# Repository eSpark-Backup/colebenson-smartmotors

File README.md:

# ColeBenson-SmartMotors
 To create a smart motor system involving CAN Interface using STM32 MCU

## Project Requirements v3.3
* The RJ11 connector for CAN should be changed with RJ45 connector. The recommended connectors and pinouts are shared by client as stated below. We need to ensure that user can plug into any of the CAN connectors (CANA or CANB) and still have daisy chain feature without hassle. We will be restricting the user to only use Straight Through cable. 
    * ### Pinout Information

    * ### Recommended Connector
        * [Digikey Link](https://www.digikey.ca/en/products/detail/molex/0855115001/2421532); [Molex Link](https://www.molex.com/en-us/products/part-detail/855115001)

    * ### Question
      We need to check if we need to restrict the user to only connect from CANA to CANA or CANB to CANB or they can also connect from CANA to CANB in daisy chain?

* Remove all Solder bridges from the design from both Top Board and Bottom board. Following bridges were sent by Japan team but they need to be ensured.
    * [Top Board]  
      SB6  
      SB3  
      SB9  
      SB4  
      SB11  
      SB7  
      SB1  
    * [Bottom Board]  
      SB2  
      SB4  
      SB6  
      SB8

* Add another high current Stepper Motor connector to the design and add it overlapping the existing connector. The suggested connector is [Digikey Link](https://www.digikey.ca/en/products/detail/jst-sales-america-inc/B4P-VH-FB-B-LF-SN/7230471)
* Change boot mode to be able to use a single 1 x 3 header with the center pin always GND.
* Change XT60 connector this connector from [Robotshop](https://ca.robotshop.com/products/xt60-connector-male-female-pair-black)

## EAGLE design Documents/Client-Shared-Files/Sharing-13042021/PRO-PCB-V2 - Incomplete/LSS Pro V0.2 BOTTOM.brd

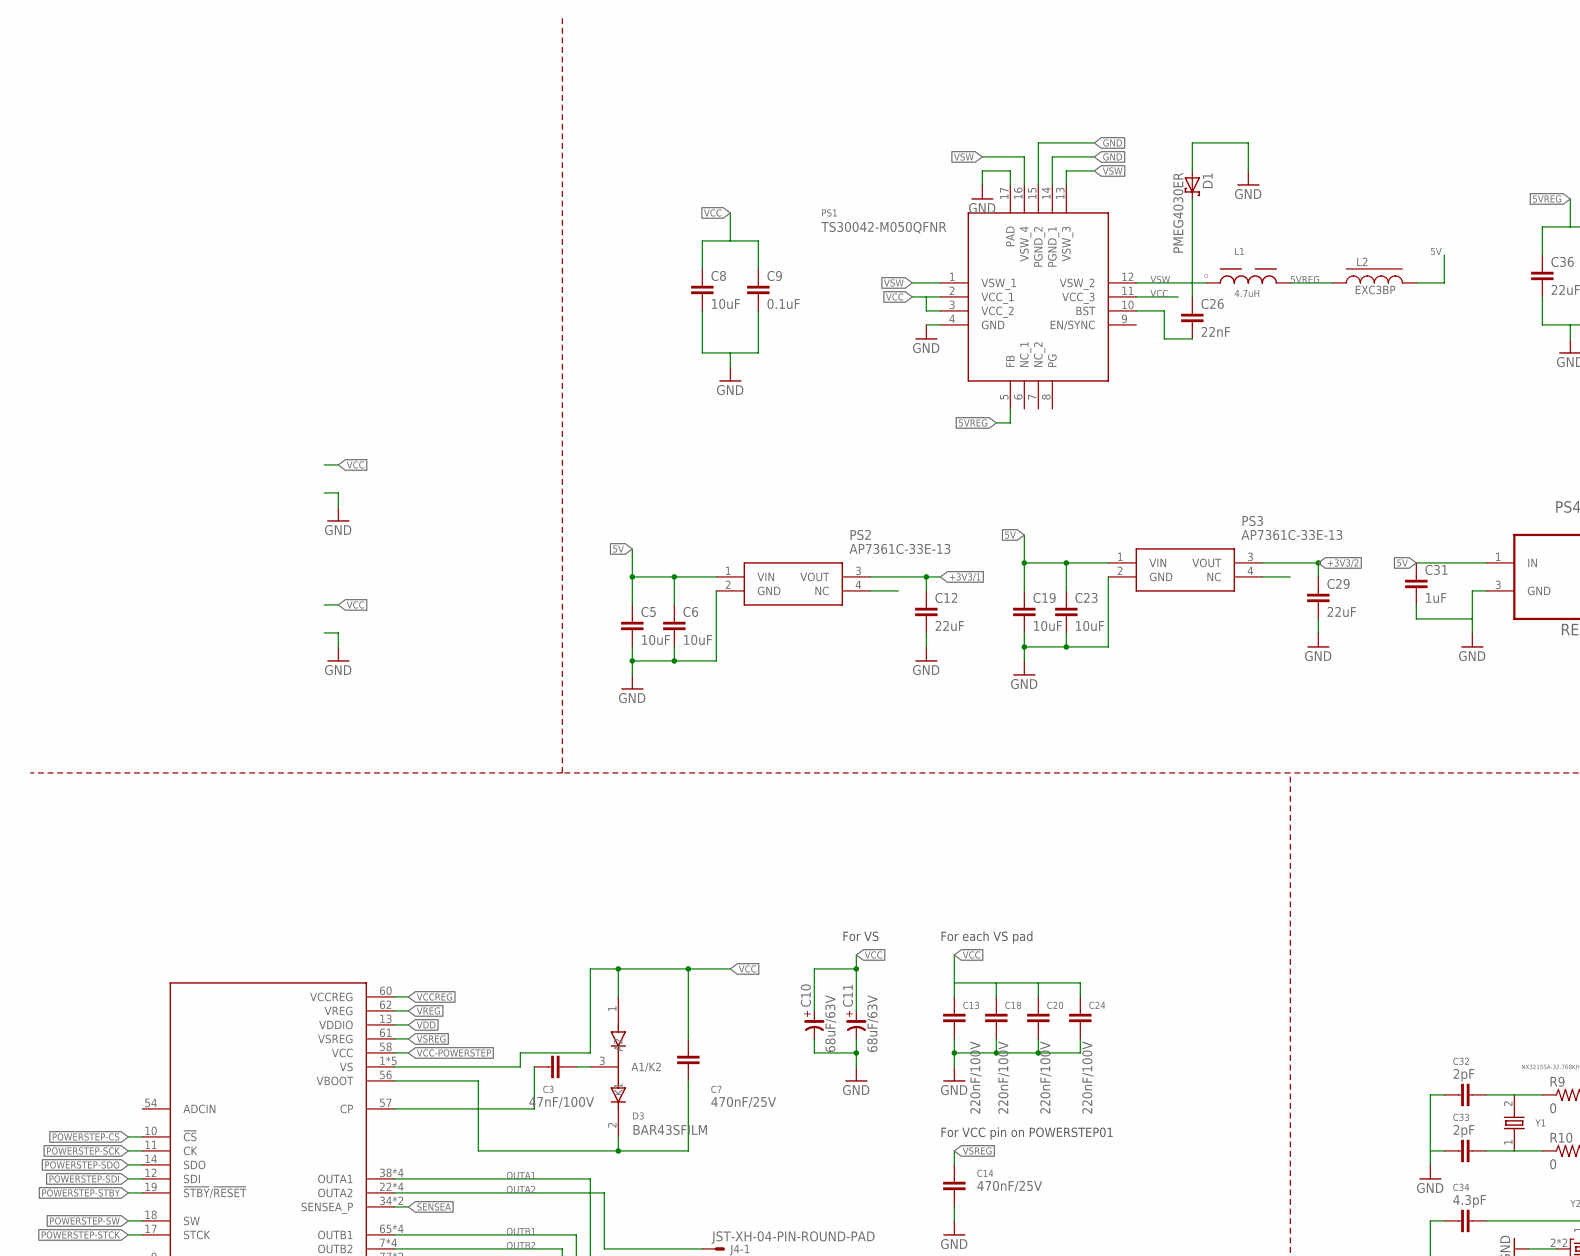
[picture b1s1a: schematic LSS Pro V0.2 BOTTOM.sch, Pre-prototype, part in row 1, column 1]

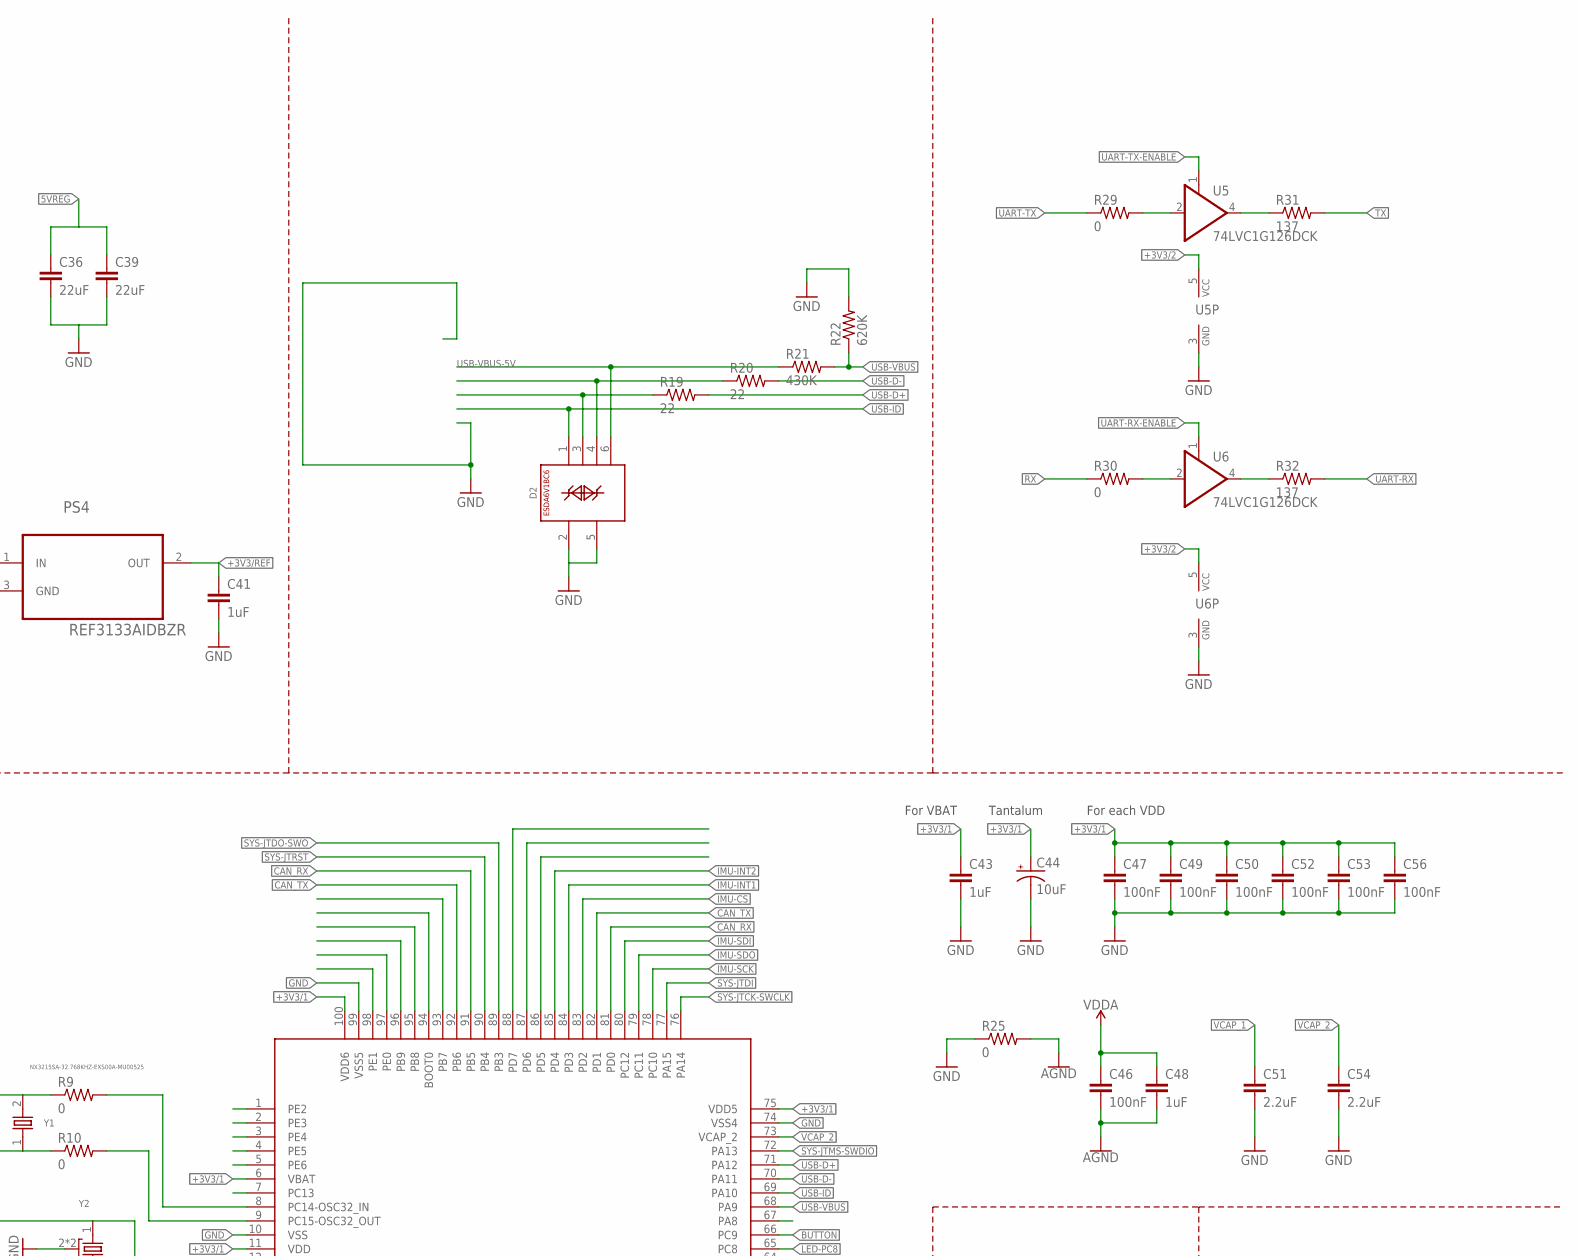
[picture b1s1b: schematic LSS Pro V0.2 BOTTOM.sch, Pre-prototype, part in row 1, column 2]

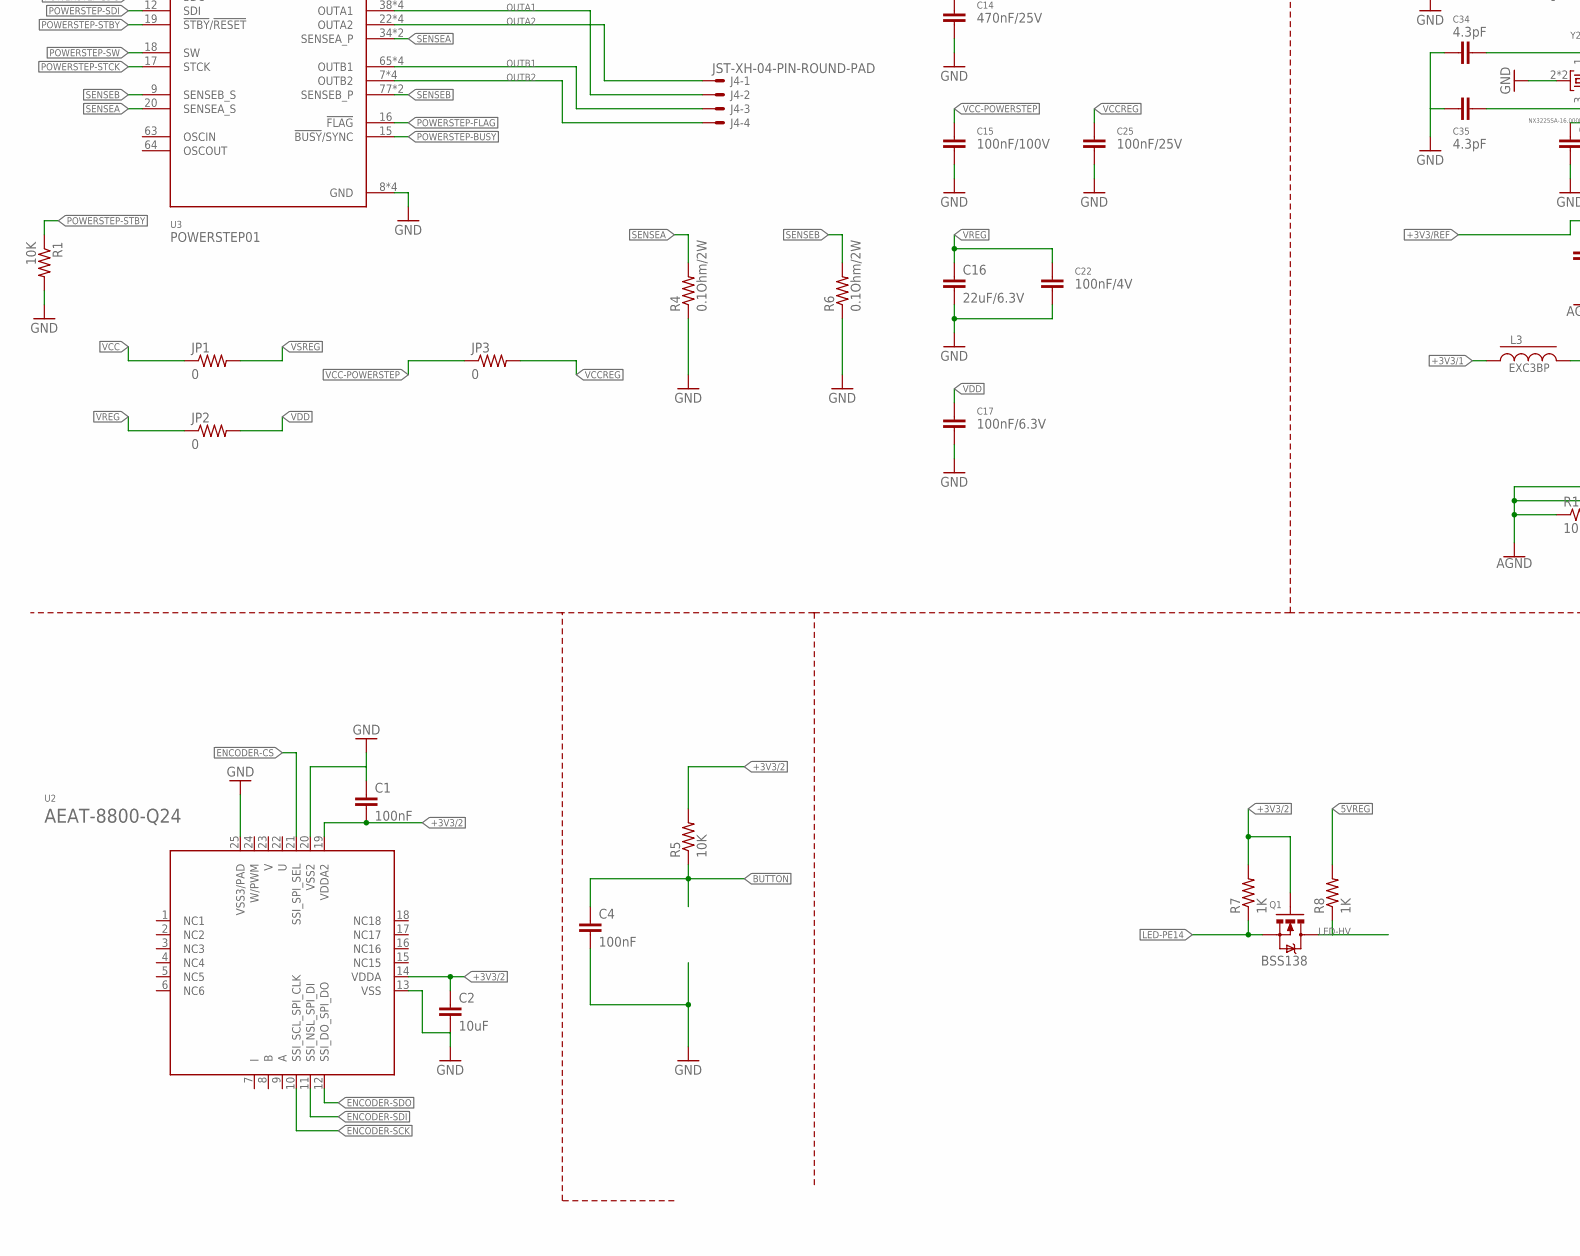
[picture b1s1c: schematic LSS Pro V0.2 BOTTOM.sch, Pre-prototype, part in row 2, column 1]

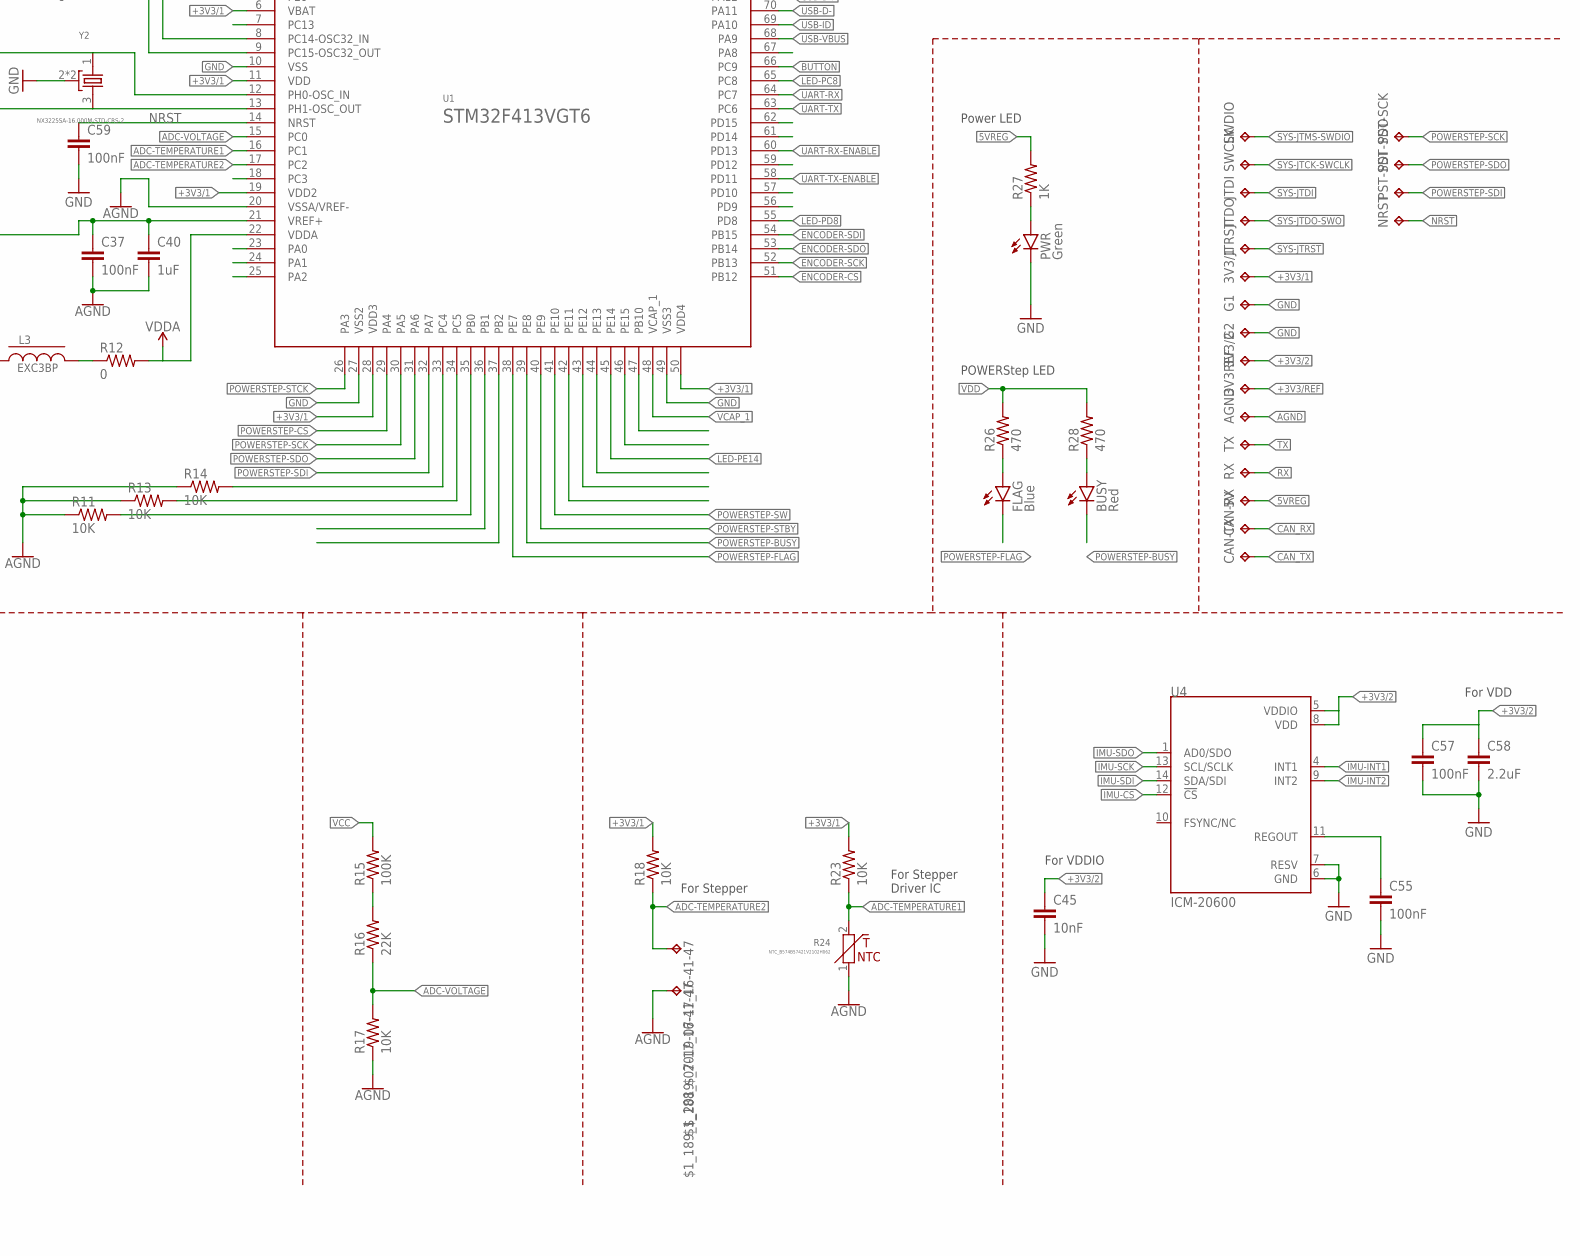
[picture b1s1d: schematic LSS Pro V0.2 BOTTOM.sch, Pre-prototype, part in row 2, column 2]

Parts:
3V3/1, 3V3/2, 3V3REF, 5V: TPTP17R; TP17R
$1_188_$_2019-07-17_16-41-47, $1_189_$_2019-07-17_16-41-47: TP-040
AGND: TPTP17R; TP17R
BUSY: Red; LED-0603
C1, C4, C37, C46, C47, C49, C50, C52, C53, C55, C56, C57, C59: 100nF; 0603-CAP
C2: 10uF; 0603-CAP
C3: 47nF/100V; 0805
C5, C6, C19, C23: 10uF; 0805
C7, C14: 470nF/25V; 0603-CAP
C8: 10uF; 1206
C9: 0.1uF; 0603-CAP
C10, C11: 68uF/63V; CSV-E/F
C12, C29, C36, C39: 22uF; 0805
C13, C18, C20, C24: 220nF/100V; 0805
C15: 100nF/100V; 0603-CAP
C16: 22uF/6.3V; 1206
C17: 100nF/6.3V; 0603-CAP
C22: 100nF/4V; 0603-CAP
C25: 100nF/25V; 0603-CAP
C26: 22nF; 0402-CAP
C31, C41: 1uF; 0805
C32, C33: 2pF; 0603-CAP
C34, C35: 4.3pF; 0603-CAP
C40, C43, C48: 1uF; 0603-CAP
C44: 10uF; EIA3216
C45: 10nF; 0603-CAP
C51, C54, C58: 2.2uF; 1206
CAN-RX: TPTP17R; TP17R
CAN-TX: TPTP17R; TP17R
D1: PMEG4030ER; SOD123W
D2: ESDA6V1BC6; SOT-23-6L
D3: BAR43SFILM; SOT105P242X150-3N
FLAG: Blue; LED-0603
G1, G2: TPTP17R; TP17R
J4: JST-XH-04-PIN-ROUND-PAD; JST-XH-04-PACKAGE-ROUND-PAD
JP1, JP2, JP3: 0; 0603-RES
JTDI: TPTP17R; TP17R
JTDO: TPTP17R; TP17R
JTRST: TPTP17R; TP17R
L1: 4.7uH; WE-PD2_5848/5820
L2, L3: EXC3BP; L0603
NRST: TPTP17R; TP17R
PS1: TS30042-M050QFNR; QFN16
PS2, PS3: AP7361C-33E-13; SOT230P700X165-4N
PS4: REF3133AIDBZR; SOT95P237X112-3N
PST-SCK: TPTP17R; TP17R
PST-SDI: TPTP17R; TP17R
PST-SDO: TPTP17R; TP17R
PWR: Green; LED-0603
Q1: BSS138; SOT23-3
R1, R11, R13, R14: 10K; 0402-RES
R4, R6: 0.1Ohm/2W; R2512
R5, R17, R18, R23: 10K; 0603-RES
R7, R8: 1K; 0603-RES
R9, R10, R12, R25, R29, R30: 0; 0603-RES
R15: 100K; 0603-RES
R16: 22K; 0603-RES
R19, R20: 22; 0603-RES
R21: 430K; 0603-RES
R22: 620K; 0603-RES
R24: NTC_B574B57421V2102H062; R0805
R26, R28: 470; 0402-RES
R27: 1K; 0402-RES
R31, R32: 137; 0603-RES
RX: TPTP17R; TP17R
SWCLK: TPTP17R; TP17R
SWDIO: TPTP17R; TP17R
TX: TPTP17R; TP17R
U1: STM32F413VGT6; LQFP100
U2: AEAT-8800-Q24; QFN24
U3: POWERSTEP01; IC_POWERSTEP01
U4: ICM-20600; PQFN50P250X300X97-14N
U5, U6: 74LVC1G126DCK; SC70-5
Y1: NX3215SA-32.768KHZ-EXS00A-MU00525; NX3215SA
Y2: NX3225SA-16.000M-STD-CRS-2; OSCCC320X250X60N

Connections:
5V: C5.1, C6.1, C19.1, C23.1, C31.1, L2.2, PS2.1 (VIN), PS3.1 (VIN), PS4.1 (IN)
5VREG: 5V.TP, C36.1, C39.1, L1.2, L2.1, PS1.5 (FB), R8.2, R27.2
+3V3/1: 3V3/1.TP, C12.1, C43.1, C44.A (+), C47.1, C49.1, C50.1, C52.1, C53.1, C56.1, L3.1, PS2.3 (VOUT), R18.2, R23.2, U1.6 (VBAT), U1.11 (VDD), U1.19 (VDD2), U1.28 (VDD3), U1.50 (VDD4), U1.75 (VDD5), U1.100 (VDD6)
+3V3/2: 3V3/2.TP, C1.2, C2.1, C29.1, C45.1, C57.1, C58.1, PS3.3 (VOUT), Q1.1 (G), R5.2, R7.2, U2.14 (VDDA), U2.19 (VDDA2), U4.5 (VDDIO), U4.8 (VDD), U5.5 (VCC), U6.5 (VCC)
+3V3/REF: 3V3REF.TP, C37.1, C40.1, C41.1, PS4.2 (OUT), U1.21 (VREF+)
ADC-TEMPERATURE1: R23.1, R24.2, U1.16 (PC1)
ADC-TEMPERATURE2: $1_188_$_2019-07-17_16-41-47.1, R18.1, U1.17 (PC2)
ADC-VOLTAGE: R16.1, R17.2, U1.15 (PC0)
AGND: $1_189_$_2019-07-17_16-41-47.1, AGND.TP, C37.2, C40.2, C46.2, C48.2, R11.1, R13.1, R14.1, R17.1, R24.1, R25.2, U1.20 (VSSA/VREF-)
BUTTON: C4.1, R5.1, U1.66 (PC9)
CAN_RX: CAN-RX.TP, U1.81 (PD0), U1.91 (PB5)
CAN_TX: CAN-TX.TP, U1.82 (PD1), U1.92 (PB6)
ENCODER-CS: U1.51 (PB12), U2.21 (SSI_SPI_SEL)
ENCODER-SCK: U1.52 (PB13), U2.10 (SSI_SCL_SPI_CLK)
ENCODER-SDI: U1.54 (PB15), U2.11 (SSI_NSL_SPI_DI)
ENCODER-SDO: U1.53 (PB14), U2.12 (SSI_DO_SPI_DO)
GND: C1.1, C2.2, C4.2, C5.2, C6.2, C8.2, C9.2, C10.-, C11.-, C12.2, C13.2, C14.2, C15.2, C16.2, C17.2, C18.2, C19.2, C20.2, C22.2, C23.2, C24.2, C25.2, C29.2, C31.2, C32.2, C33.2, C34.2, C35.2, C36.2, C39.2, C41.2, C43.2, C44.C (-), C45.2, C47.2, C49.2, C50.2, C51.2, C52.2, C53.2, C54.2, C55.2, C56.2, C57.2, C58.2, C59.2, D1.2 (A), D2.2, D2.5, G1.TP, G2.TP, PS1.4 (GND), PS1.14 (PGND_1), PS1.15 (PGND_2), PS1.17 (PAD), PS2.2 (GND), PS3.2 (GND), PS4.3 (GND), PWR.C, R1.2, R4.1, R6.1, R22.2, R25.1, U1.10 (VSS), U1.27 (VSS2), U1.49 (VSS3), U1.74 (VSS4), U1.99 (VSS5), U2.13 (VSS), U2.20 (VSS2), U2.25 (VSS3/PAD), U3.8 (GND), U3.21 (GND), U3.59 (GND), U3.EPAD9 (GND), U4.6 (GND), U4.7 (RESV), U5.3 (GND), U6.3 (GND), Y2.2 (GND), Y2.4 (GND)
IMU-CS: U1.83 (PD2), U4.12 (!CS)
IMU-INT1: U1.84 (PD3), U4.4 (INT1)
IMU-INT2: U1.85 (PD4), U4.9 (INT2)
IMU-SCK: U1.78 (PC10), U4.13 (SCL/SCLK)
IMU-SDI: U1.80 (PC12), U4.14 (SDA/SDI)
IMU-SDO: U1.79 (PC11), U4.1 (AD0/SDO)
LED-HV: Q1.3 (D), R8.1
LED-PC8: U1.65 (PC8)
LED-PD8: U1.55 (PD8)
LED-PE14: Q1.2 (S), R7.1, U1.45 (PE14)
unnamed: R30.2, U6.2 (I)
unnamed: R9.2, U1.8 (PC14-OSC32_IN)
unnamed: R10.2, U1.9 (PC15-OSC32_OUT)
unnamed: L3.2, R12.1
unnamed: R32.1, U6.4 (O)
unnamed: C34.1, U1.12 (PH0-OSC_IN), Y2.1
unnamed: C35.1, U1.13 (PH1-OSC_OUT), Y2.3
unnamed: PWR.A, R27.1
unnamed: R29.2, U5.2 (I)
unnamed: R31.1, U5.4 (O)
unnamed: C32.1, R9.1, Y1.2
unnamed: C33.1, R10.1, Y1.1
unnamed: FLAG.A, R26.1
unnamed: C3.1, U3.57 (CP)
unnamed: R15.1, R16.2
unnamed: C55.1, U4.11 (REGOUT)
unnamed: BUSY.A, R28.1
unnamed: D2.4, R20.1
unnamed: D2.3, R19.1
unnamed: C3.2, D3.3 (A1/K2)
unnamed: R14.2, U1.33 (PC4)
unnamed: R13.2, U1.34 (PC5)
unnamed: R11.2, U1.35 (PB0)
unnamed: C7.2, D3.2 (K1), U3.56 (VBOOT)
unnamed: C26.2, PS1.10 (BST)
NRST: C59.1, NRST.TP, U1.14 (NRST)
OUTA1: J4.2, U3.38 (OUTA1), U3.42 (OUTA1), U3.53 (OUTA1), U3.EPAD4 (OUTA1)
OUTA2: J4.1, U3.22 (OUTA2), U3.33 (OUTA2), U3.37 (OUTA2), U3.EPAD3 (OUTA2)
OUTB1: J4.3, U3.65 (OUTB1), U3.76 (OUTB1), U3.80 (OUTB1), U3.EPAD7 (OUTB1)
OUTB2: J4.4, U3.7 (OUTB2), U3.81 (OUTB2), U3.85 (OUTB2), U3.EPAD8 (OUTB2)
POWERSTEP-BUSY: BUSY.C, U1.39 (PE8), U3.15 (!BUSY!/SYNC)
POWERSTEP-CS: U1.29 (PA4), U3.10 (!CS)
POWERSTEP-FLAG: FLAG.C, U1.38 (PE7), U3.16 (!FLAG)
POWERSTEP-SCK: PST-SCK.TP, U1.30 (PA5), U3.11 (CK)
POWERSTEP-SDI: PST-SDI.TP, U1.32 (PA7), U3.12 (SDI)
POWERSTEP-SDO: PST-SDO.TP, U1.31 (PA6), U3.14 (SDO)
POWERSTEP-STBY: R1.1, U1.40 (PE9), U3.19 (!STBY!/!RESET)
POWERSTEP-STCK: U1.26 (PA3), U3.17 (STCK)
POWERSTEP-SW: U1.41 (PE10), U3.18 (SW)
RX: R30.1, RX.TP
SENSEA: R4.2, U3.20 (SENSEA_S), U3.34 (SENSEA_P), U3.39 (SENSEA_P)
SENSEB: R6.2, U3.9 (SENSEB_S), U3.77 (SENSEB_P), U3.82 (SENSEB_P)
SYS-JTCK-SWCLK: SWCLK.TP, U1.76 (PA14)
SYS-JTDI: JTDI.TP, U1.77 (PA15)
SYS-JTDO-SWO: JTDO.TP, U1.89 (PB3)
SYS-JTMS-SWDIO: SWDIO.TP, U1.72 (PA13)
SYS-JTRST: JTRST.TP, U1.90 (PB4)
TX: R31.2, TX.TP
UART-RX: R32.2, U1.64 (PC7)
UART-RX-ENABLE: U1.60 (PD13), U6.1 (OE)
UART-TX: R29.1, U1.63 (PC6)
UART-TX-ENABLE: U1.58 (PD11), U5.1 (OE)
USB-D+: R19.2, U1.71 (PA12)
USB-D-: R20.2, U1.70 (PA11)
USB-ID: D2.1, U1.69 (PA10)
USB-VBUS: R21.2, R22.1, U1.68 (PA9)
USB-VBUS-5V: D2.6, R21.1
VCAP_1: C51.1, U1.48 (VCAP_1)
VCAP_2: C54.1, U1.73 (VCAP_2)
VCC: C7.1, C8.1, C9.1, C10.+, C11.+, C13.1, C18.1, C20.1, C24.1, D3.1 (A2), JP1.1, PS1.2 (VCC_1), PS1.3 (VCC_2), PS1.11 (VCC_3), R15.2, U3.1 (VS), U3.23 (VS), U3.43 (VS), U3.55 (VS), U3.66 (VS)
VCC-POWERSTEP: C15.1, JP3.1, U3.58 (VCC)
VCCREG: C25.1, JP3.2, U3.60 (VCCREG)
VDD: C17.1, JP2.2, R26.2, R28.2, U3.13 (VDDIO)
VDDA: C46.1, C48.1, R12.2, U1.22 (VDDA)
VREG: C16.1, C22.1, JP2.1, U3.62 (VREG)
VSREG: C14.1, JP1.2, U3.61 (VSREG)
VSW: C26.1, D1.1 (K), L1.1, PS1.1 (VSW_1), PS1.12 (VSW_2), PS1.13 (VSW_3), PS1.16 (VSW_4)

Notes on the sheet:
For VBAT
Tantalum
For each VDD
For VS
For each VS pad
For VCC pin on POWERSTEP01
For VDD
For VDDIO
For Stepper Driver IC
Power LED
POWERStep LED
For Stepper

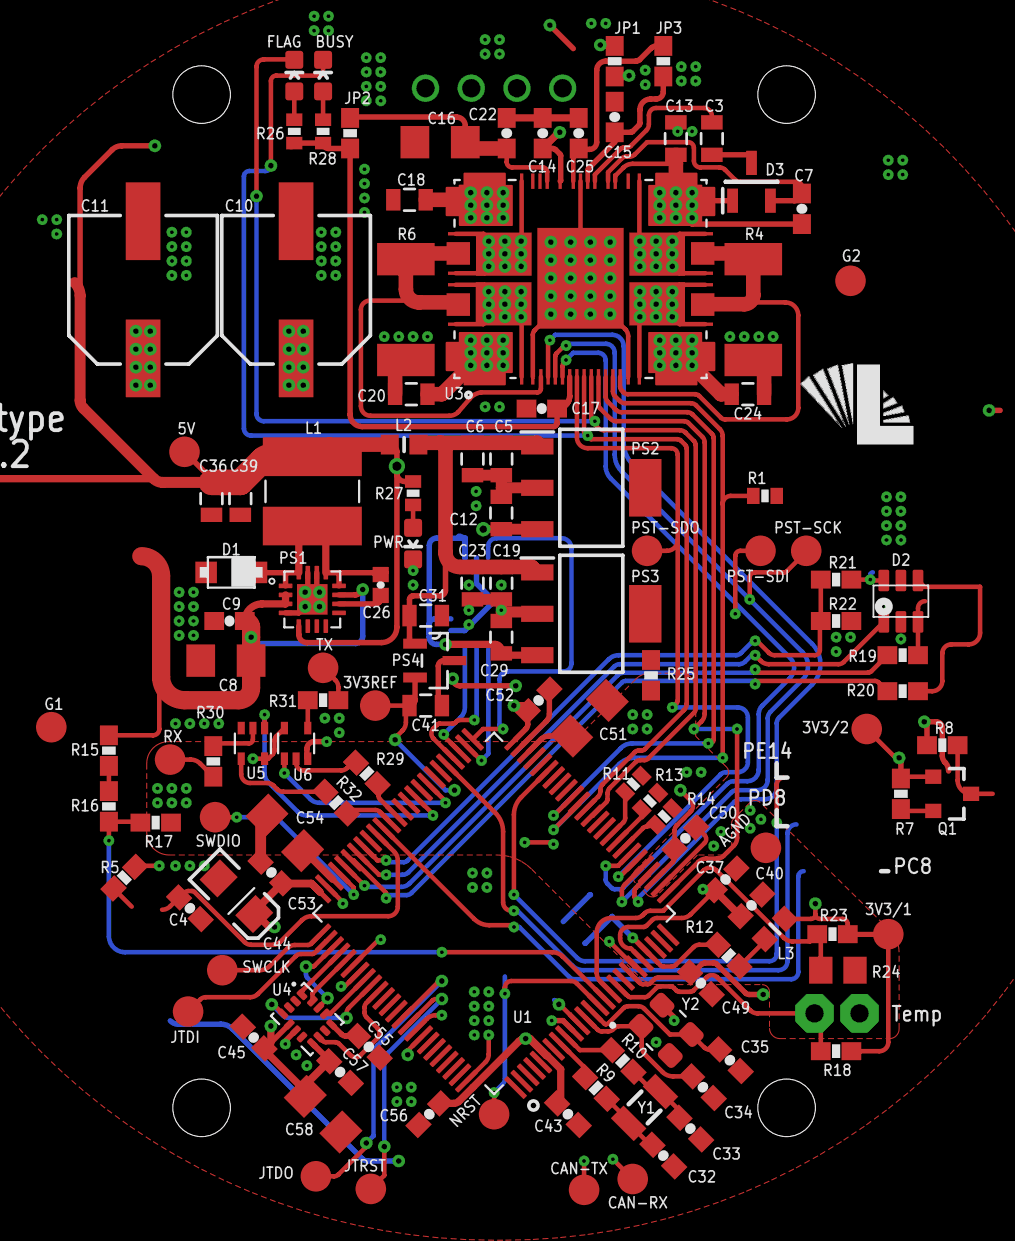
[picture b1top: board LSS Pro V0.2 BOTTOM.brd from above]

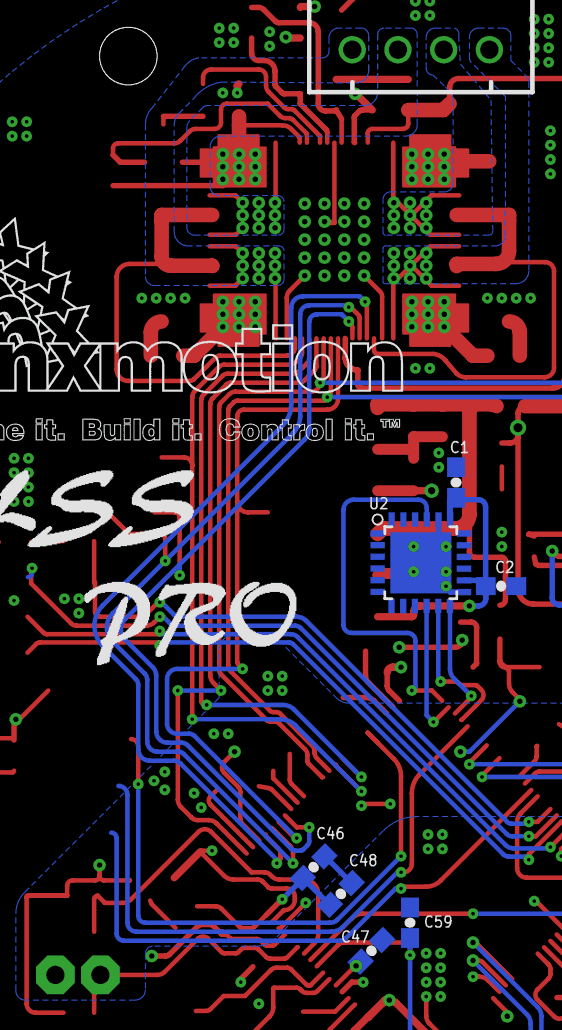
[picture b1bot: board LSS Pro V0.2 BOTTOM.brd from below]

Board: 4 copper layers, 131 parts (8 on the bottom side), 92 nets.

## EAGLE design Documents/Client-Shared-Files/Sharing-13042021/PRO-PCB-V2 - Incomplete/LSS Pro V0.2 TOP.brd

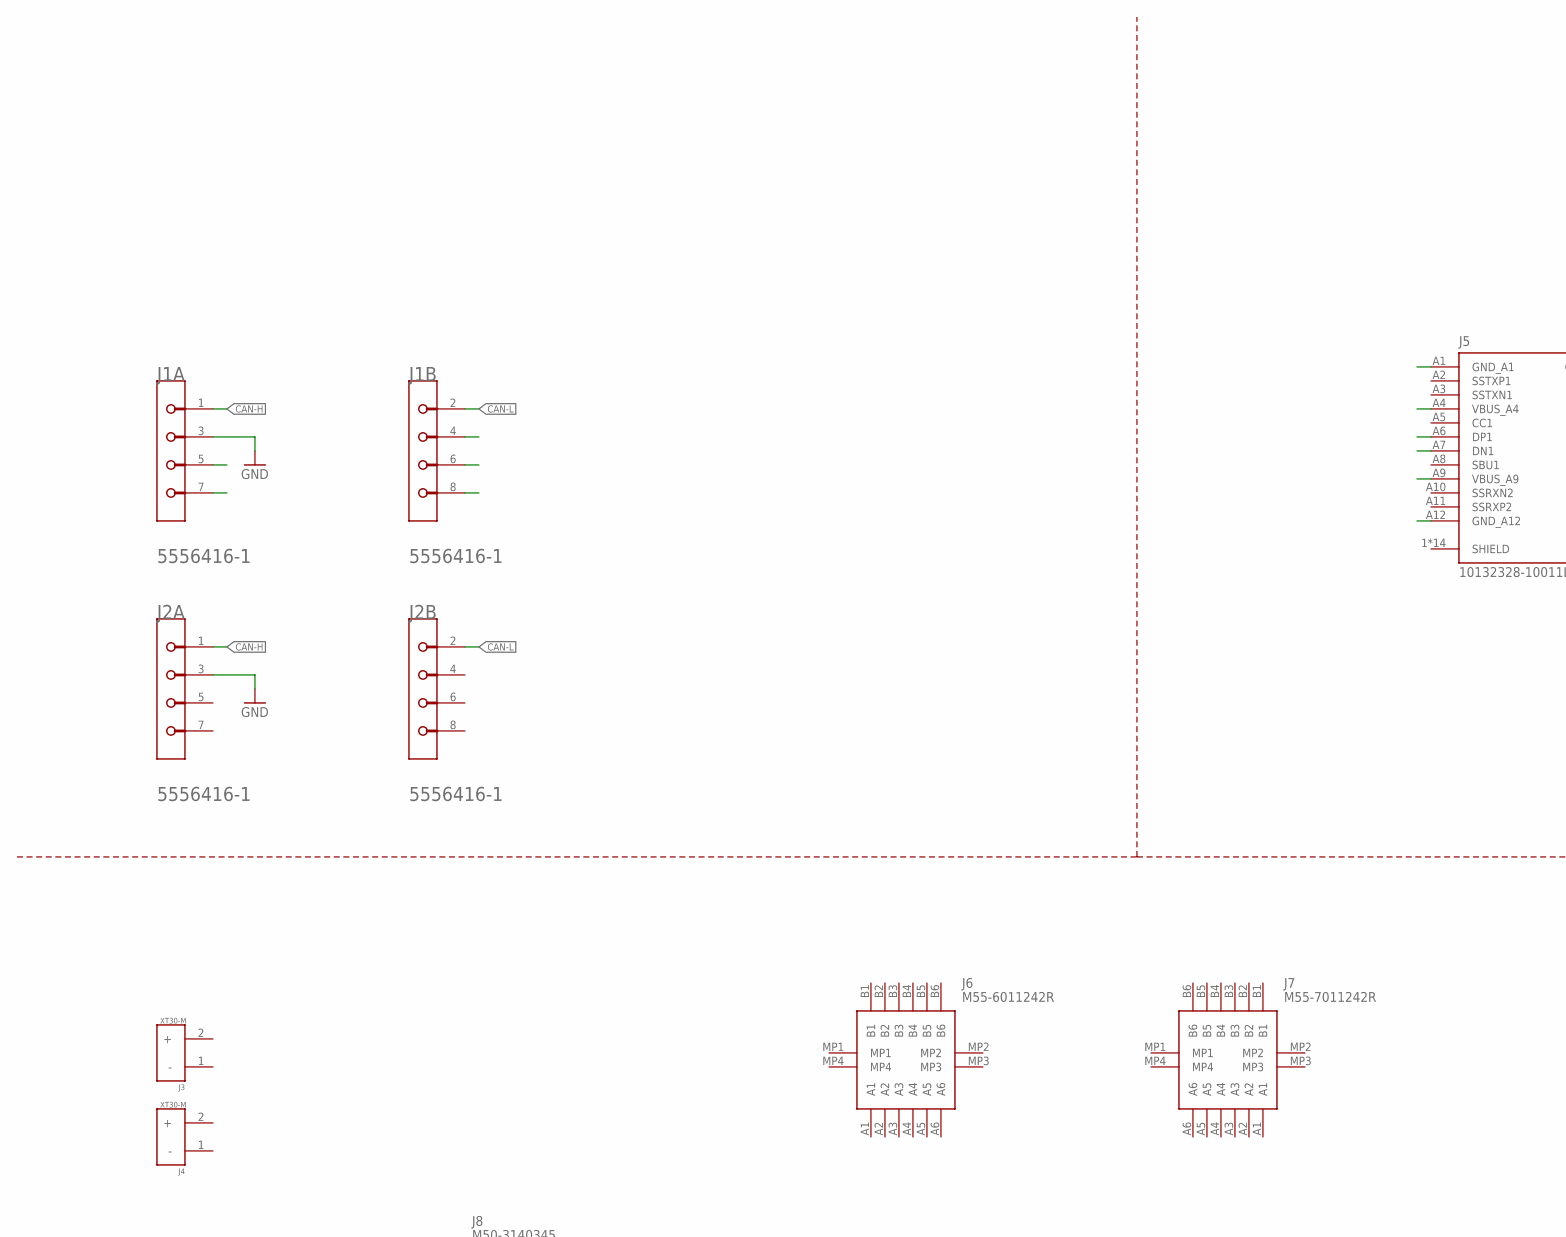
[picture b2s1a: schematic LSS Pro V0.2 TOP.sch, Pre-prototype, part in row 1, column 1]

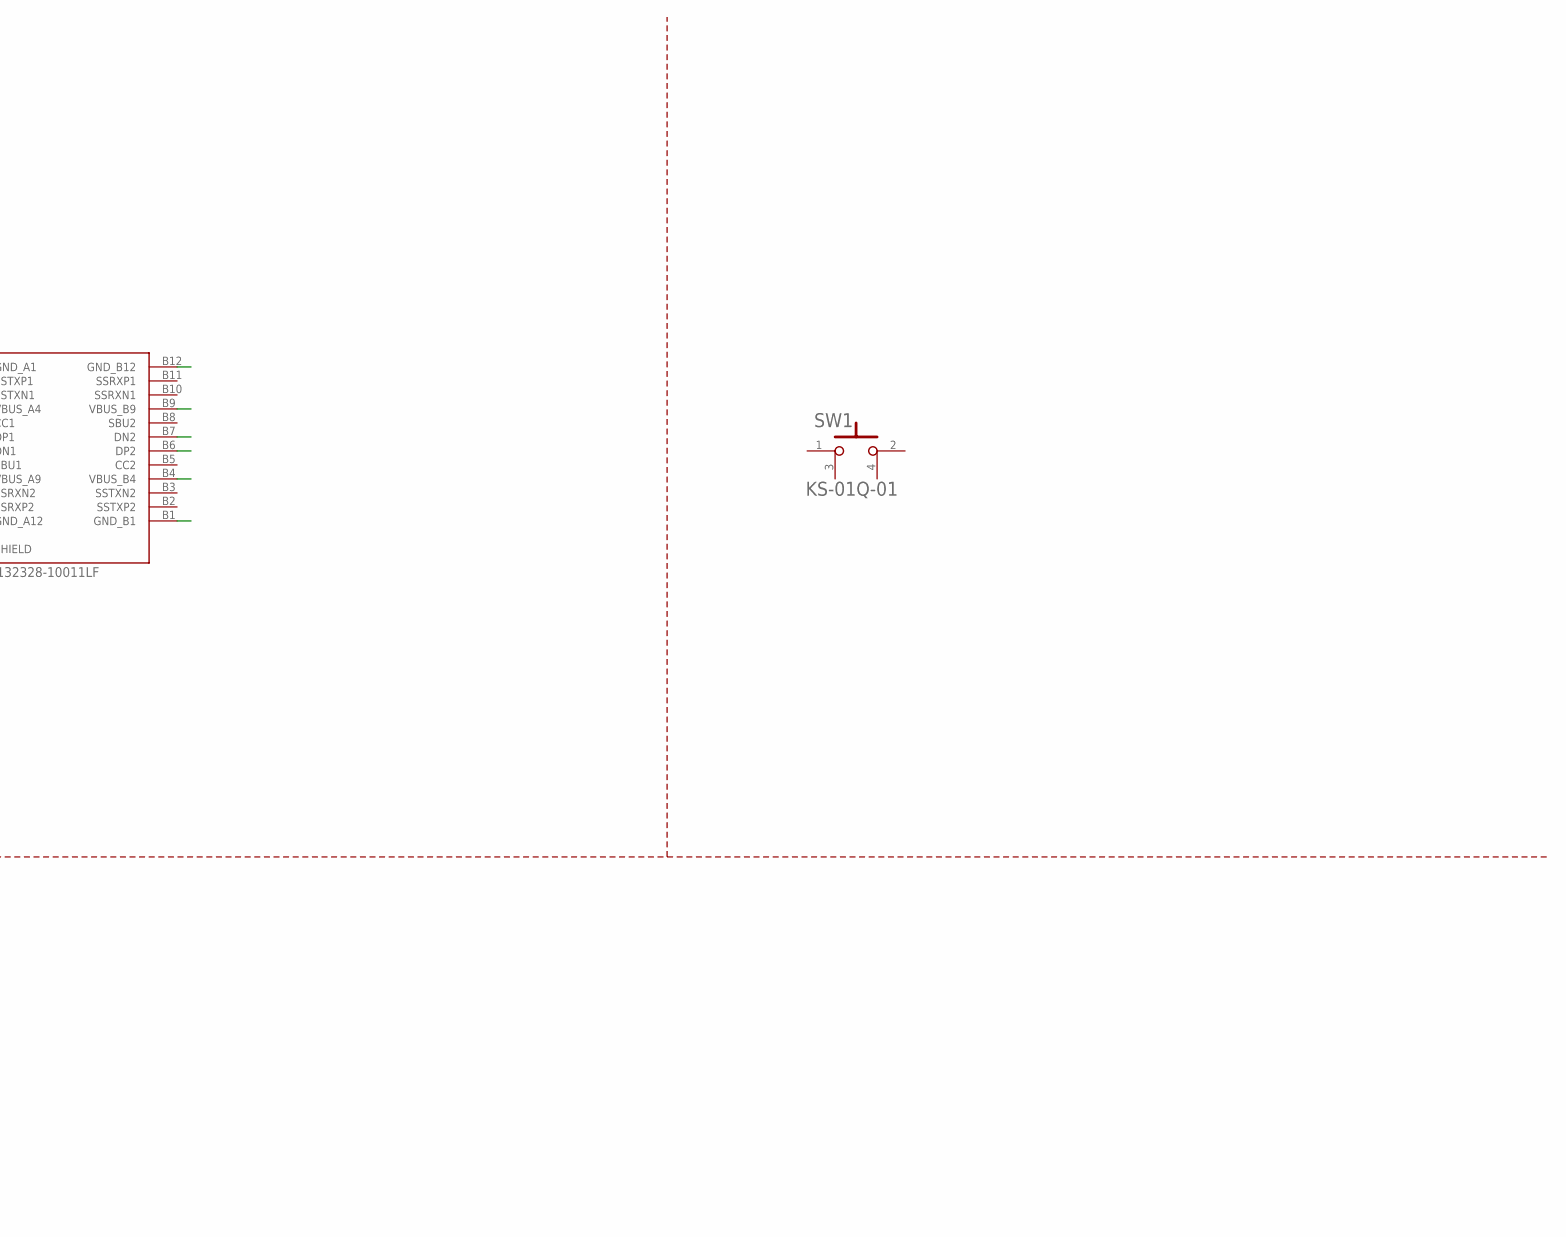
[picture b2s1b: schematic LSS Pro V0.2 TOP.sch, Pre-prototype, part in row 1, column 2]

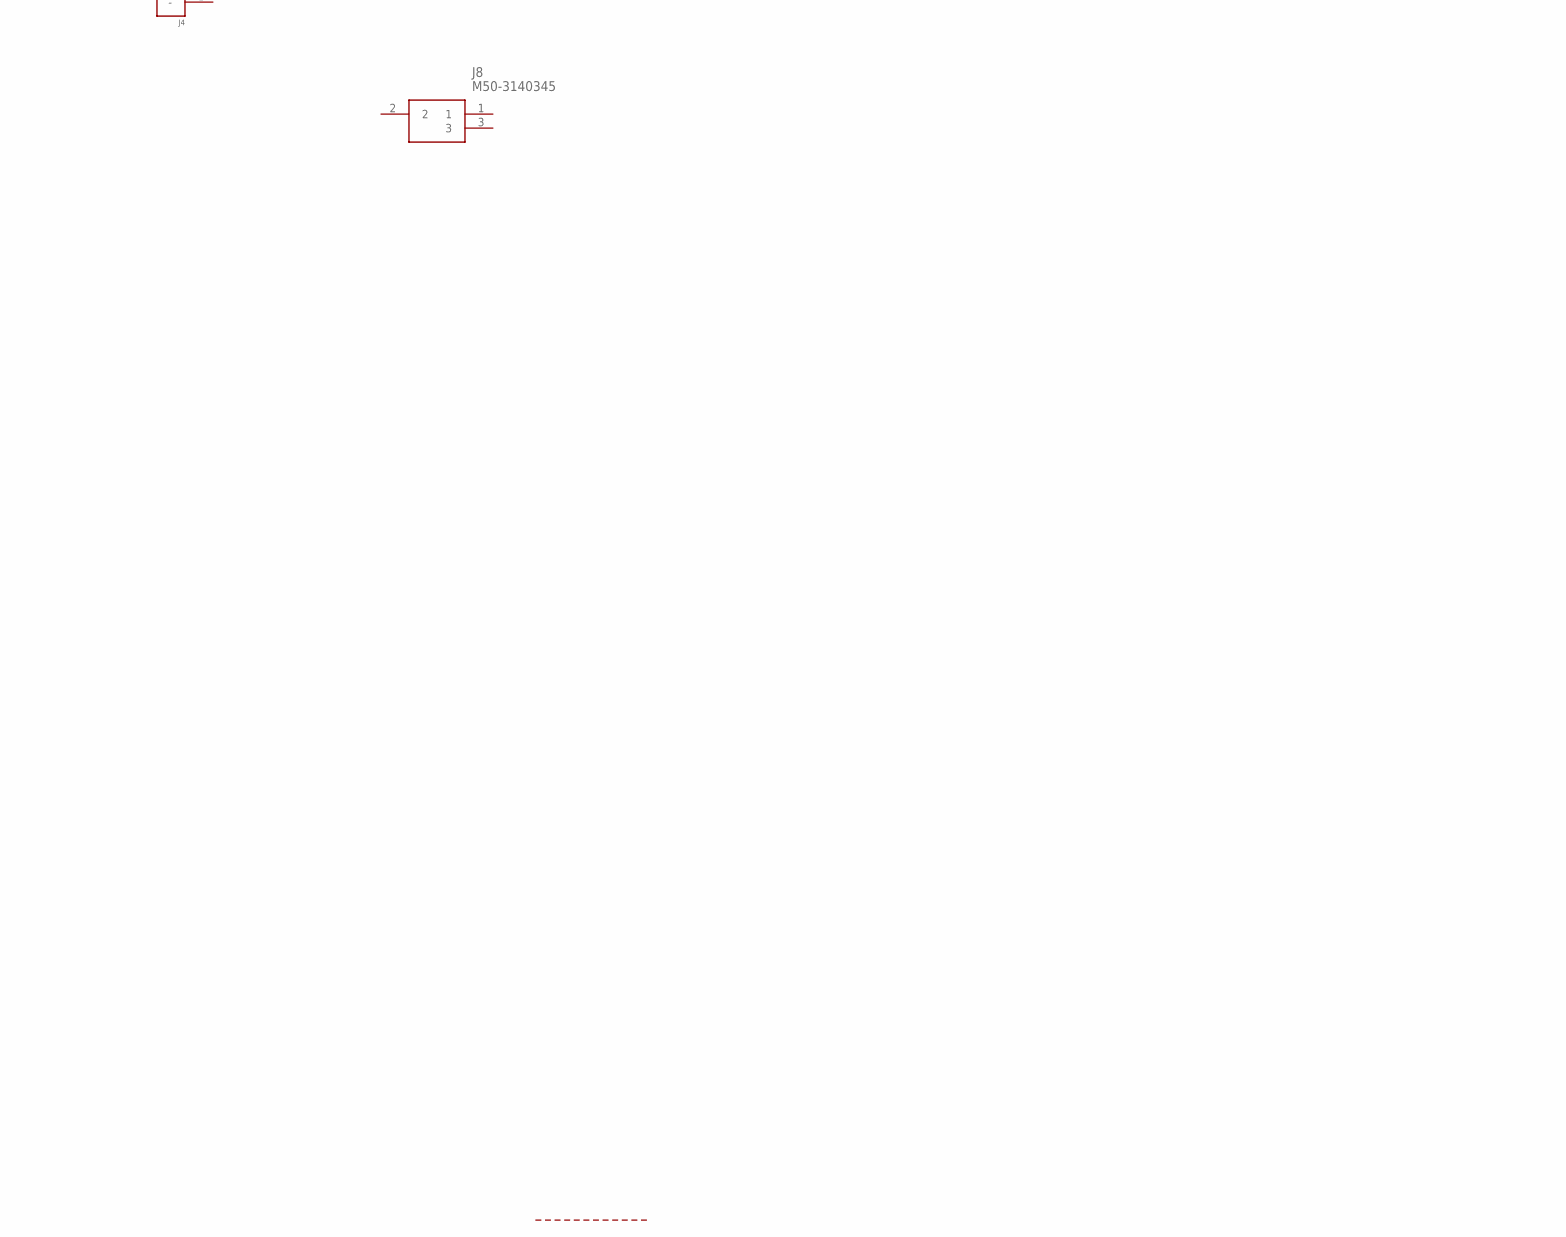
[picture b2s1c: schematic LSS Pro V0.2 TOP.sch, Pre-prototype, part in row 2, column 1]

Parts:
J1, J2: TE_5556416-1TE_5556416-1_0_0; TE_5556416-1_0
J3, J4: XT30-M
J5: 10132328-10011LF; AMPHENOL_10132328-10011LF
J6: M55-6011242R; M556011242R
J7: M55-7011242R; M557011242R
J8: M50-3140345; M503140345
SW1: E-SWITCH_KS-01Q-01E-SWITCH_KS-01Q-01_0_0; E-SWITCH_KS-01Q-01_0

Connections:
CAN-H: J1.1, J2.1
CAN-L: J1.2, J2.2
GND: J1.3, J2.3

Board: 4 copper layers, 9 parts (0 on the bottom side), 3 nets, no tracks yet.

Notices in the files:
parts and their libraries:
SparkFun-Capacitors: Licensing: Creative Commons ShareAlike 4.0 International - https://creativecommons.org/licenses/by-sa/4.0
EMCComponents: Copyright: Würth Elektronik
FaBo-Supply: Released under the Creative Commons Attribution-ShareAlike 4.0 License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
rc-master-smd: Copyright (C) 2007, Bob Starr
